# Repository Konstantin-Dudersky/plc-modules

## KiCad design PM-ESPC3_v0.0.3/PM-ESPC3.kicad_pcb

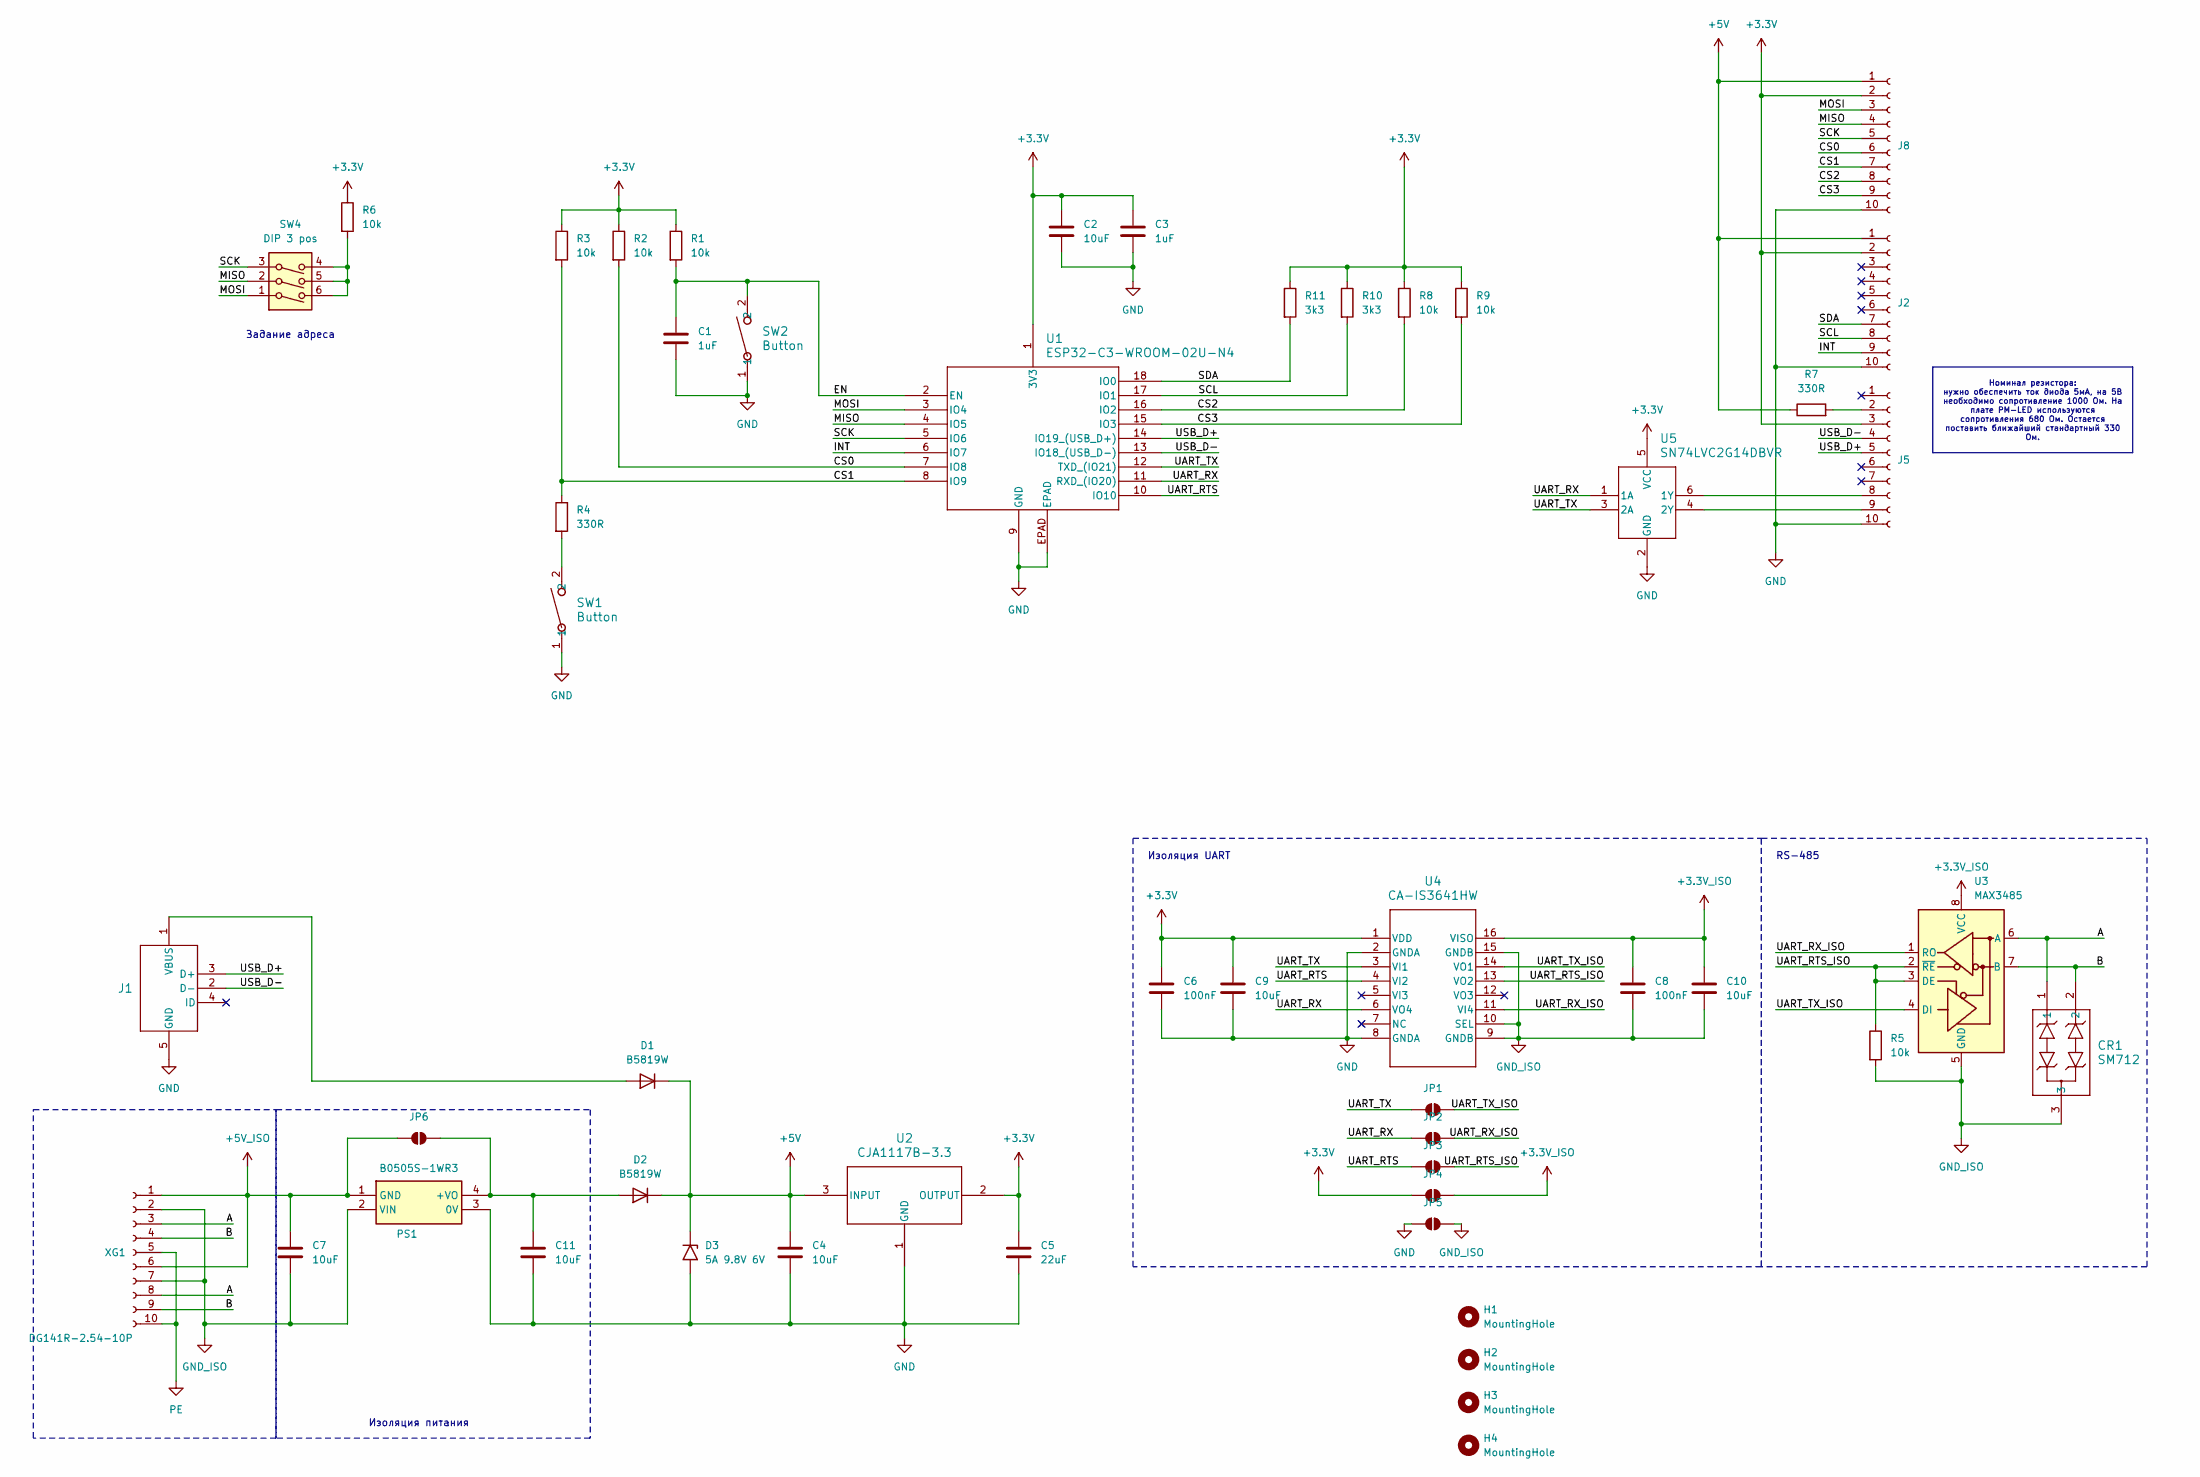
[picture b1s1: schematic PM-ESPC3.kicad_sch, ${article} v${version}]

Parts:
C1, C3: 1uF; C_1206_3216Metric_Pad1.33x1.80mm_HandSolder; part_ipn C_1uF_16V_1206
C2, C4, C7, C9, C10, C11: 10uF; C_1206_3216Metric_Pad1.33x1.80mm_HandSolder; part_ipn C_10uF_16V_1206
C5: 22uF; C_1206_3216Metric_Pad1.33x1.80mm_HandSolder; part_ipn C_22uF_16V_1206
C6, C8: 100nF; C_1206_3216Metric_Pad1.33x1.80mm_HandSolder; part_ipn C_100nF_50V_1206
CR1: SM712; SOT23-3_LTF
D1, D2: B5819W; D_SOD-123; part_ipn B5819W
D3: 5A 9.8V 6V; D_SOD-323_HandSoldering; part_ipn LESD3Z5.0T1G
H1, H2, H3, H4: MountingHole; MountingHole_2.1mm
J1: U254-051T-4BH83-S1S; CONN5_H83-S1S_XKB; part_ipn U254-051T-4BH83-S1S
J2, J5, J8: AFA07-S10FCC-00; CONN10_AFA07-S10_JUS; part_ipn AFA07-S10FCC-00
JP1, JP2, JP3, JP4, JP5, JP6: SolderJumper_2_Open; SolderJumper-2_P1.3mm_Open_RoundedPad1.0x1.5mm
PS1: B0505S-1WR3; B0505S1WR3; Manufacturer_Part_Number B0505S-1WR3
R1, R2, R3, R5, R6, R8, R9: 10k; R_1206_3216Metric_Pad1.30x1.75mm_HandSolder; part_ipn R_10k_1206_1%
R4, R7: 330R; R_1206_3216Metric_Pad1.30x1.75mm_HandSolder; part_ipn R_330R_1206_1%
R10, R11: 3k3; R_1206_3216Metric_Pad1.30x1.75mm_HandSolder; part_ipn R_3k3_1206_1%
SW1, SW2: Button; SW_TS-1088_XNP-M; part_ipn TS-1088-AR02016
SW4: DIP 3 pos; DA03BLP; part_ipn DA-03BLP
U1: ESP32-C3-WROOM-02U-N4; ESP32-C3-WROOM-02U_EXP; part_ipn ESP32-C3-WROOM-02U-N4
U2: CJA1117B-3.3; SOT-89-3; part_ipn CJA1117B-3.3
U3: MAX3485; SOIC-8_3.9x4.9mm_P1.27mm
U4: CA-IS3641HW; SOIC16-WBW_CLG-M; part_ipn CA-IS3641HW
U5: SN74LVC2G14DBVR; DBV6-M
XG1: DG141R-2.54-10P; part_ipn DG141R-2.54-10P

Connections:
+3.3V: C2.2, C3.1, C5.1, C6.1, C9.1, J2.2, J5.3, J8.2, JP4.1 (A), R1.1, R2.1, R3.1, R6.1, R8.1, R9.1, R10.1, R11.1, U1.1 (3V3), U2.2 (OUTPUT), U4.1 (VDD), U5.5 (VCC)
+3.3V_ISO: C8.1, C10.1, JP4.2 (B), U3.8 (VCC), U4.16 (VISO)
+5V: C4.1, D1.1 (K), D2.1 (K), D3.1 (A1), J2.1, J8.1, R7.1, U2.3 (INPUT)
+5V_ISO: C7.1, JP6.1 (A), PS1.1 (GND), XG1.1, XG1.6
/A: CR1.1, U3.6 (A), XG1.3, XG1.8
/B: CR1.2, U3.7 (B), XG1.4, XG1.9
/CS0: J8.6, R2.2, U1.7 (IO8)
/CS1: J8.7, R3.2, R4.1, U1.8 (IO9)
/CS2: J8.8, R8.2, U1.16 (IO2)
/CS3: J8.9, R9.2, U1.15 (IO3)
/EN: C1.1, R1.2, SW2.2, U1.2 (EN)
/INT: J2.9, U1.6 (IO7)
/MISO: J8.4, SW4.2, U1.4 (IO5)
/MOSI: J8.3, SW4.1, U1.3 (IO4)
/SCK: J8.5, SW4.3, U1.5 (IO6)
/SCL: J2.8, R10.2, U1.17 (IO1)
/SDA: J2.7, R11.2, U1.18 (IO0)
/UART_RTS: JP3.1 (A), U1.10 (IO10), U4.4 (VI2)
/UART_RTS_ISO: JP3.2 (B), R5.1, U3.2 (~RE), U3.3 (DE), U4.13 (VO2)
/UART_RX: JP2.1 (A), U1.11 (RXD_(IO20)), U4.6 (VO4), U5.1 (1A)
/UART_RX_ISO: JP2.2 (B), U3.1 (RO), U4.11 (VI4)
/UART_TX: JP1.1 (A), U1.12 (TXD_(IO21)), U4.3 (VI1), U5.3 (2A)
/UART_TX_ISO: JP1.2 (B), U3.4 (DI), U4.14 (VO1)
/USB_D+: J1.3 (D+), J5.5, U1.14 (IO19_(USB_D+))
/USB_D-: J1.2 (D-), J5.4, U1.13 (IO18_(USB_D-))
GND: C1.2, C2.1, C3.2, C4.2, C5.2, C6.2, C9.2, C11.2, D3.2 (A2), J1.5 (GND), J2.10, J5.10, J8.10, JP5.1 (A), PS1.3 (0V), SW1.1, SW2.1, U1.9 (GND), U1.EPAD, U2.1 (GND), U4.2 (GNDA), U4.8 (GNDA), U5.2 (GND)
GND_ISO: C7.2, C8.2, C10.2, CR1.3, JP5.2 (B), PS1.2 (VIN), R5.2, U3.5 (GND), U4.9 (GNDB), U4.10 (SEL), U4.15 (GNDB), XG1.2, XG1.7
unnamed: D1.2 (A), J1.1 (VBUS)
unnamed: C11.1, D2.2 (A), JP6.2 (B), PS1.4 (+VO)
unnamed: J5.2, R7.2
unnamed: J5.8, U5.6 (1Y)
unnamed: J5.9, U5.4 (2Y)
unnamed: R4.2, SW1.2
unnamed: R6.2, SW4.4, SW4.5, SW4.6
PE: XG1.5, XG1.10

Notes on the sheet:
Номинал резистора: нужно обеспечить ток диода 5мА, на 5В необходимо сопротивление 1000 Ом. На плате PM-LED используются сопротивления 680 Ом. Остается поставить ближайший стандартный 330 Ом.
Задание адреса
RS-485
Изоляция UART
Изоляция питания

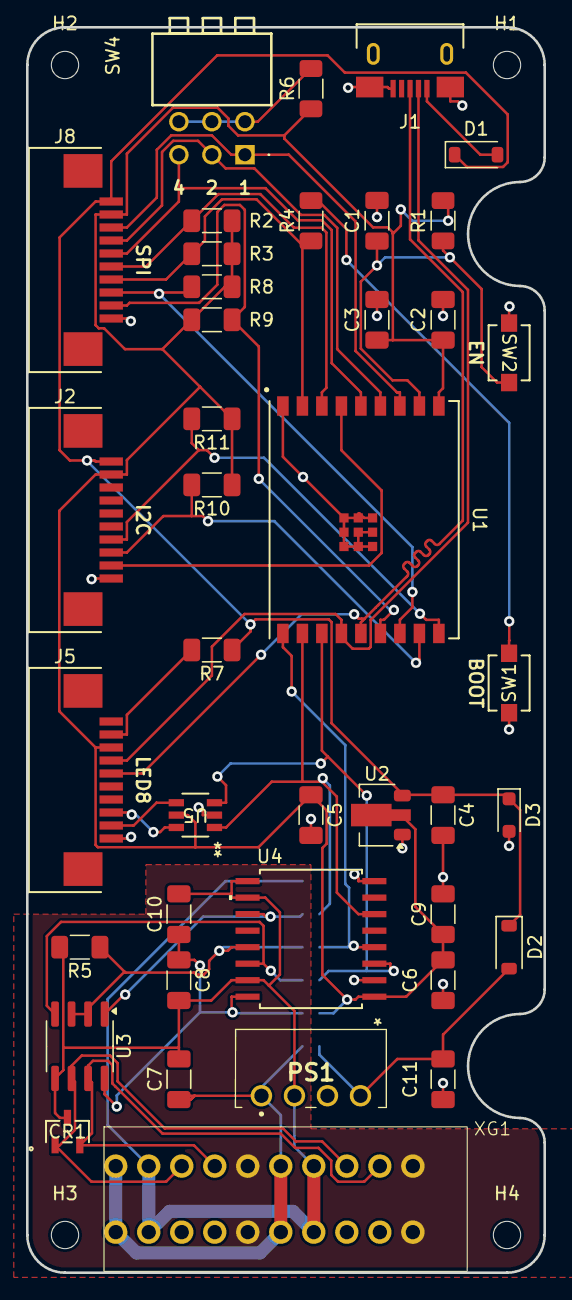
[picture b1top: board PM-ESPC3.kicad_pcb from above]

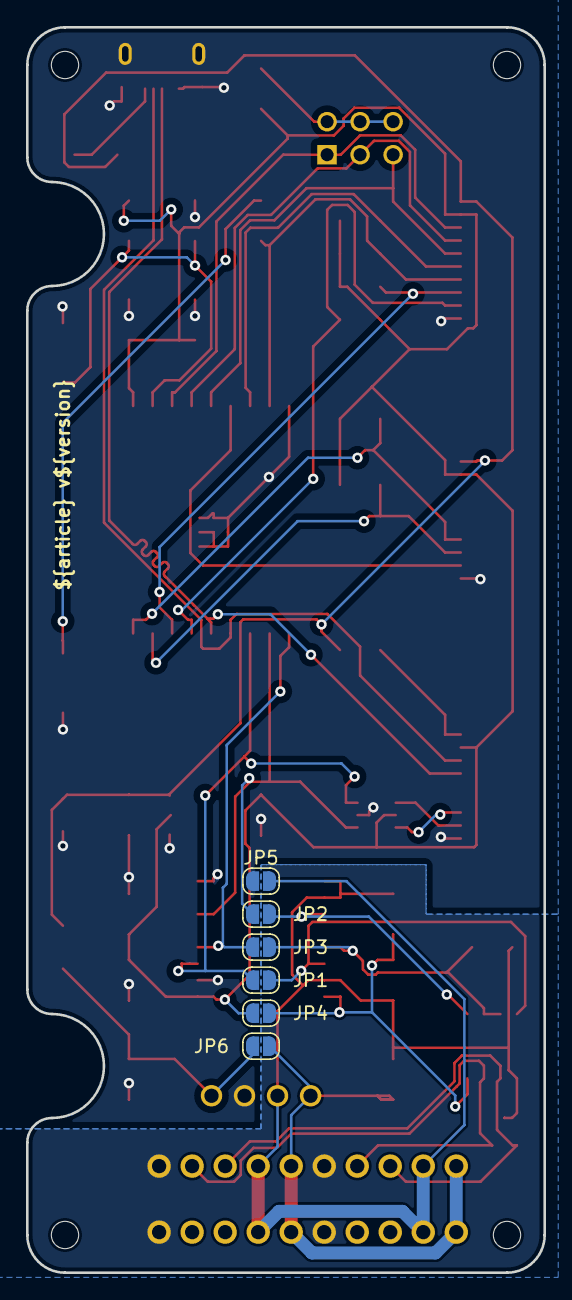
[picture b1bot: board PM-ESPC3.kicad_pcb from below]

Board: 2 copper layers, 39.8 x 95.8 mm, 50 parts (6 on the bottom side), 35 nets.

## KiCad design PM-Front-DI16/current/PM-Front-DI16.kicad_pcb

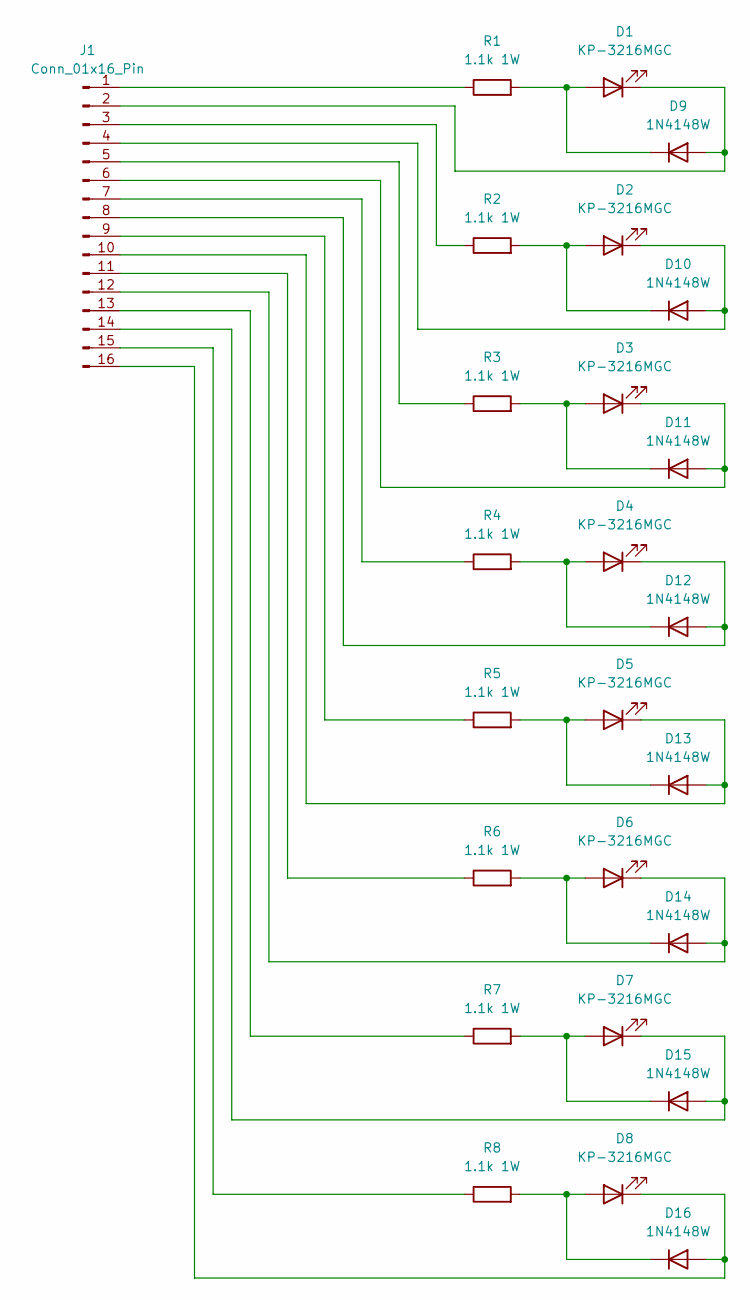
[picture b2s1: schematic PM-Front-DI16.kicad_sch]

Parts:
D1, D2, D3, D4, D5, D6, D7, D8: KP-3216MGC; LED_1206_3216Metric; MfrPart KP-3216MGC
D9, D10, D11, D12, D13, D14, D15, D16: 1N4148W; D_SOD-123; MfrPart 1N4148W
J1: Conn_01x16_Pin; PinHeader_1x16_P2.54mm_Horizontal
R1, R2, R3, R4, R5, R6, R7, R8: 1.1k 1W; R_2512_6332Metric_Pad1.40x3.35mm_HandSolder; MfgPart FRC2512F1101TS

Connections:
unnamed: D1.2 (A), D9.1 (K), R1.2
unnamed: D1.1 (K), D9.2 (A), J1.2
unnamed: D2.1 (K), D10.2 (A), J1.4
unnamed: D2.2 (A), D10.1 (K), R2.2
unnamed: D3.1 (K), D11.2 (A), J1.6
unnamed: D3.2 (A), D11.1 (K), R3.2
unnamed: D4.1 (K), D12.2 (A), J1.8
unnamed: D4.2 (A), D12.1 (K), R4.2
unnamed: D5.1 (K), D13.2 (A), J1.10
unnamed: D5.2 (A), D13.1 (K), R5.2
unnamed: D6.1 (K), D14.2 (A), J1.12
unnamed: D6.2 (A), D14.1 (K), R6.2
unnamed: D7.1 (K), D15.2 (A), J1.14
unnamed: D7.2 (A), D15.1 (K), R7.2
unnamed: D8.1 (K), D16.2 (A), J1.16
unnamed: D8.2 (A), D16.1 (K), R8.2
unnamed: J1.1, R1.1
unnamed: J1.3, R2.1
unnamed: J1.5, R3.1
unnamed: J1.7, R4.1
unnamed: J1.9, R5.1
unnamed: J1.11, R6.1
unnamed: J1.13, R7.1
unnamed: J1.15, R8.1

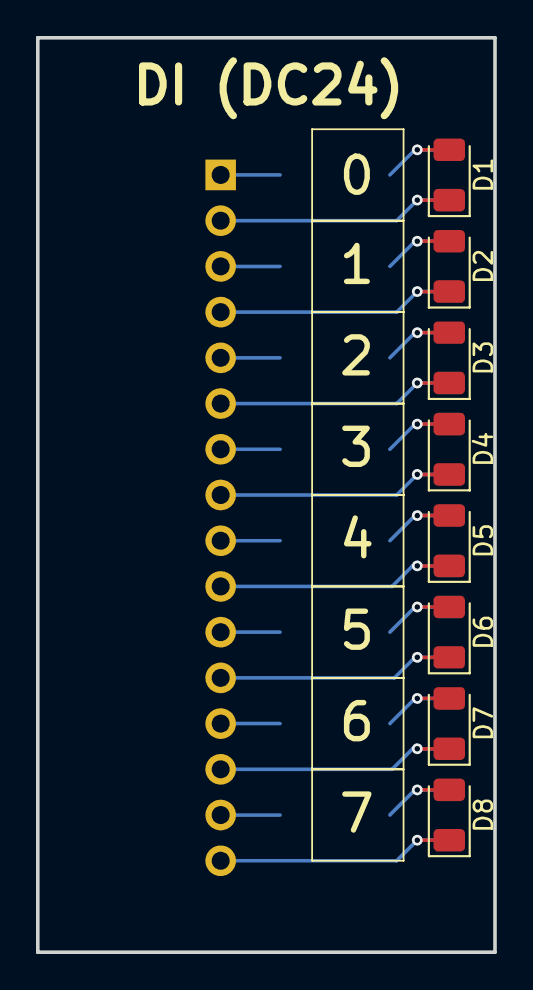
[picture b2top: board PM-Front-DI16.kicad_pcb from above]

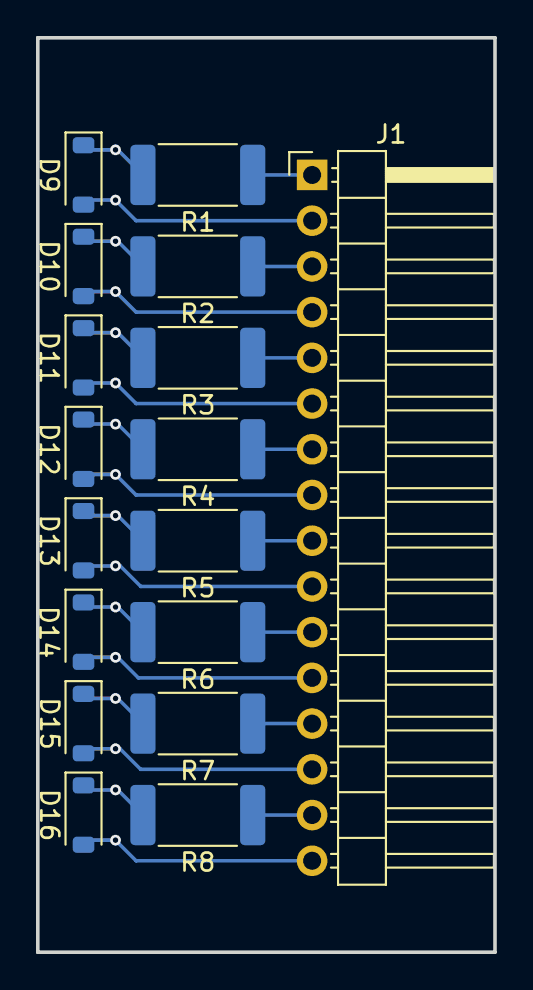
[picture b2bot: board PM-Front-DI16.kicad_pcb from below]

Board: 2 copper layers, 25.4 x 50.8 mm, 25 parts (17 on the bottom side), 24 nets.

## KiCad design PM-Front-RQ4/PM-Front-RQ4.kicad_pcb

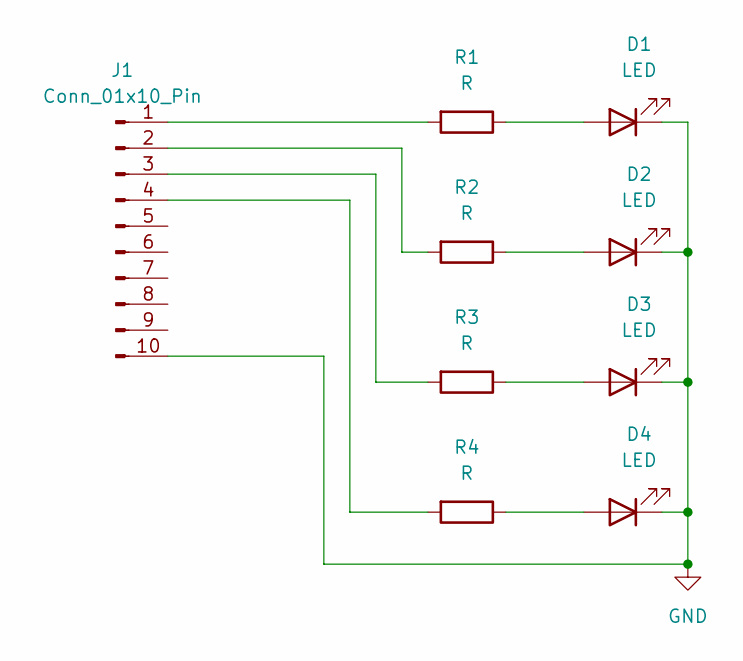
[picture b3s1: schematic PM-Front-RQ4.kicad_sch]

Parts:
D1, D2, D3, D4: LED; LED_1206_3216Metric
J1: Conn_01x10_Pin; PinHeader_1x10_P2.54mm_Horizontal
R1, R2, R3, R4: R; R_1206_3216Metric_Pad1.30x1.75mm_HandSolder

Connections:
GND: D1.1 (K), D2.1 (K), D3.1 (K), D4.1 (K), J1.10
unnamed: D1.2 (A), R1.1
unnamed: D2.2 (A), R2.1
unnamed: D3.2 (A), R3.1
unnamed: D4.2 (A), R4.1
unnamed: J1.1, R1.2
unnamed: J1.2, R2.2
unnamed: J1.3, R3.2
unnamed: J1.4, R4.2

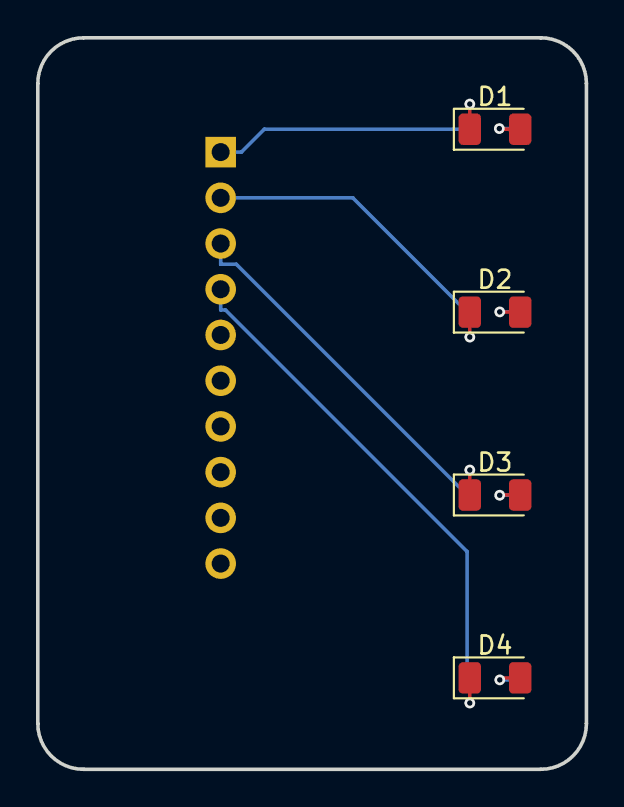
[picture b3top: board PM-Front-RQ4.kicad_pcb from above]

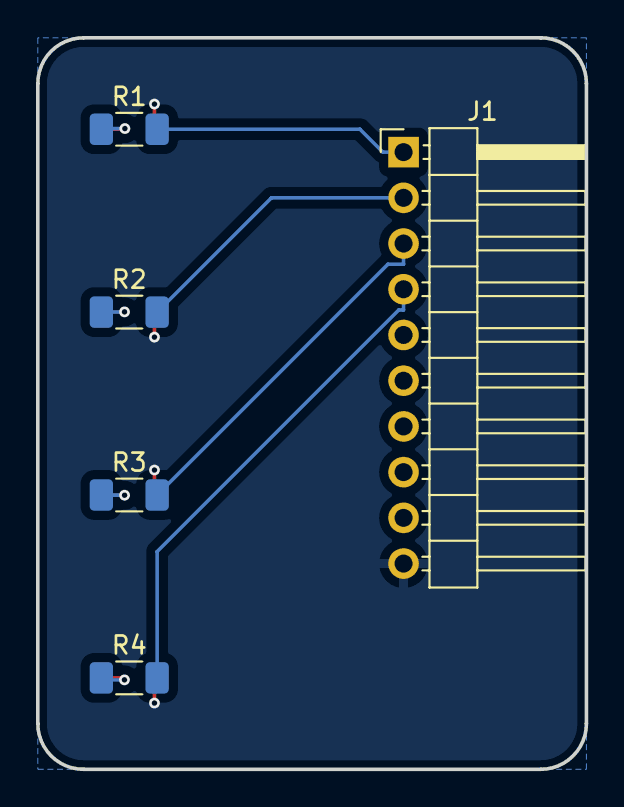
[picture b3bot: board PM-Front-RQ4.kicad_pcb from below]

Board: 2 copper layers, 30.5 x 40.6 mm, 9 parts (5 on the bottom side), 9 nets.

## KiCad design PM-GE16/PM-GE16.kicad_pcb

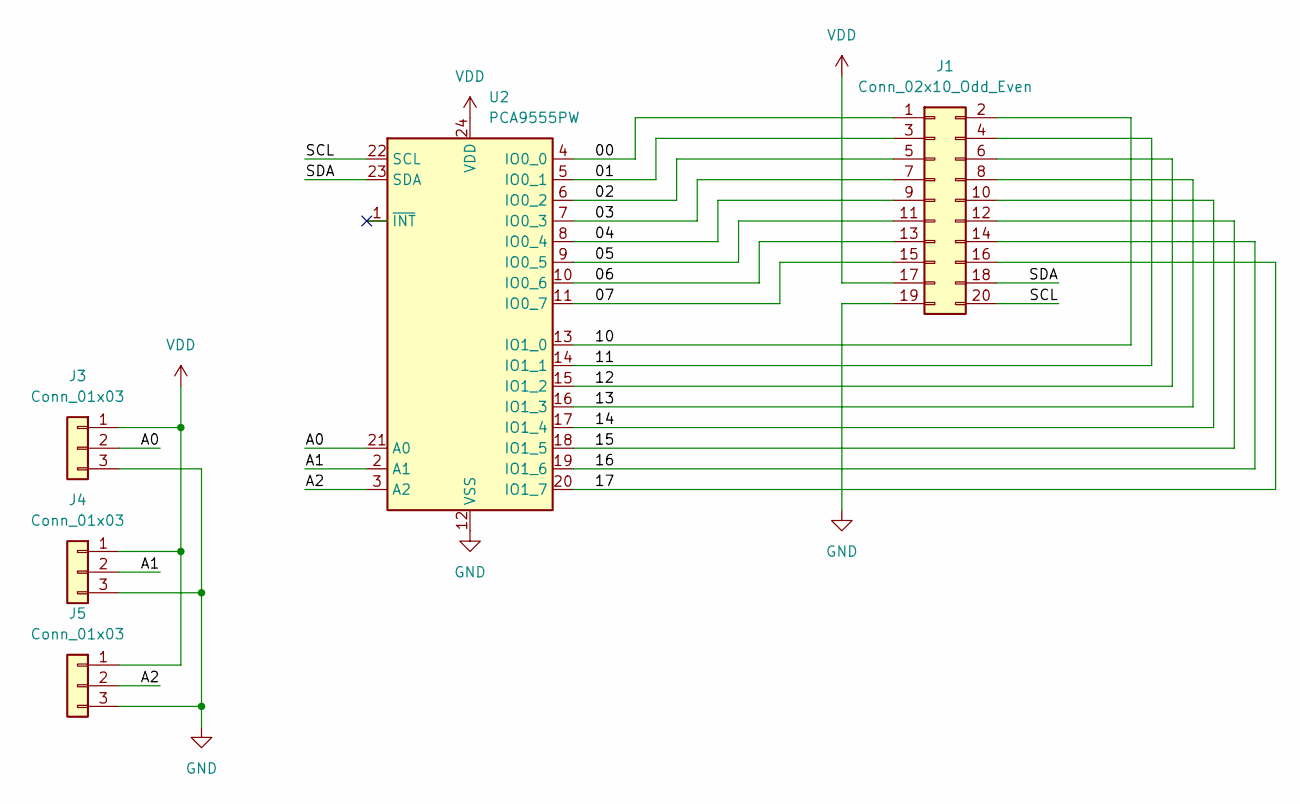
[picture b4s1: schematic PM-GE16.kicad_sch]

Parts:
J1: Conn_02x10_Odd_Even; PinHeader_2x10_P2.54mm_Vertical_SMD
J3, J4, J5: Conn_01x03; PinHeader_1x03_P2.54mm_Vertical_SMD_Pin1Left
U2: PCA9555PW; TSSOP-24_4.4x7.8mm_P0.65mm; MPN PCA9555PW

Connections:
/00: J1.1, U2.4 (IO0_0)
/01: J1.3, U2.5 (IO0_1)
/02: J1.5, U2.6 (IO0_2)
/03: J1.7, U2.7 (IO0_3)
/04: J1.9, U2.8 (IO0_4)
/05: J1.11, U2.9 (IO0_5)
/06: J1.13, U2.10 (IO0_6)
/07: J1.15, U2.11 (IO0_7)
/10: J1.2, U2.13 (IO1_0)
/11: J1.4, U2.14 (IO1_1)
/12: J1.6, U2.15 (IO1_2)
/13: J1.8, U2.16 (IO1_3)
/14: J1.10, U2.17 (IO1_4)
/15: J1.12, U2.18 (IO1_5)
/16: J1.14, U2.19 (IO1_6)
/17: J1.16, U2.20 (IO1_7)
/A0: J3.2, U2.21 (A0)
/A1: J4.2, U2.2 (A1)
/A2: J5.2, U2.3 (A2)
/SCL: J1.20, U2.22 (SCL)
/SDA: J1.18, U2.23 (SDA)
GND: J1.19, J3.3, J4.3, J5.3, U2.12 (VSS)
VDD: J1.17, J3.1, J4.1, J5.1, U2.24 (VDD)

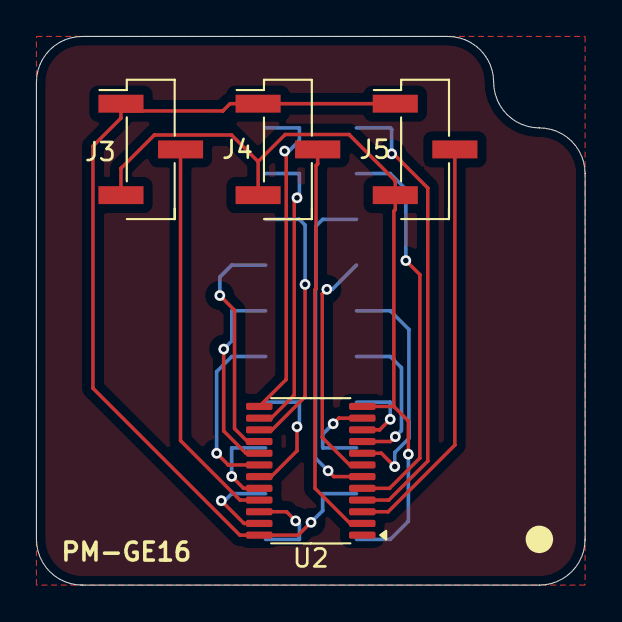
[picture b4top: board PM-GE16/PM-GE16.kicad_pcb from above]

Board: 2 copper layers, 30.5 x 30.5 mm, 5 parts (1 on the bottom side), 23 nets.

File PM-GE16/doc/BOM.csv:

Reference,Value,Footprint,Qty,NextPCB_url,NextPCB_price
J1,Conn_02x10_Odd_Even,Connector_PinHeader_2.54mm:PinHeader_2x10_P2.54mm_Vertical_SMD,1,,
"J3,J4,J5",Conn_01x03,Connector_PinHeader_2.54mm:PinHeader_1x03_P2.54mm_Vertical_SMD_Pin1Left,3,,
U2,PCA9555PW,Package_SO:TSSOP-24_4.4x7.8mm_P0.65mm,1,https://www.hqonline.com/product-detail/enzhipu-nxp--pca9555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,0.75761

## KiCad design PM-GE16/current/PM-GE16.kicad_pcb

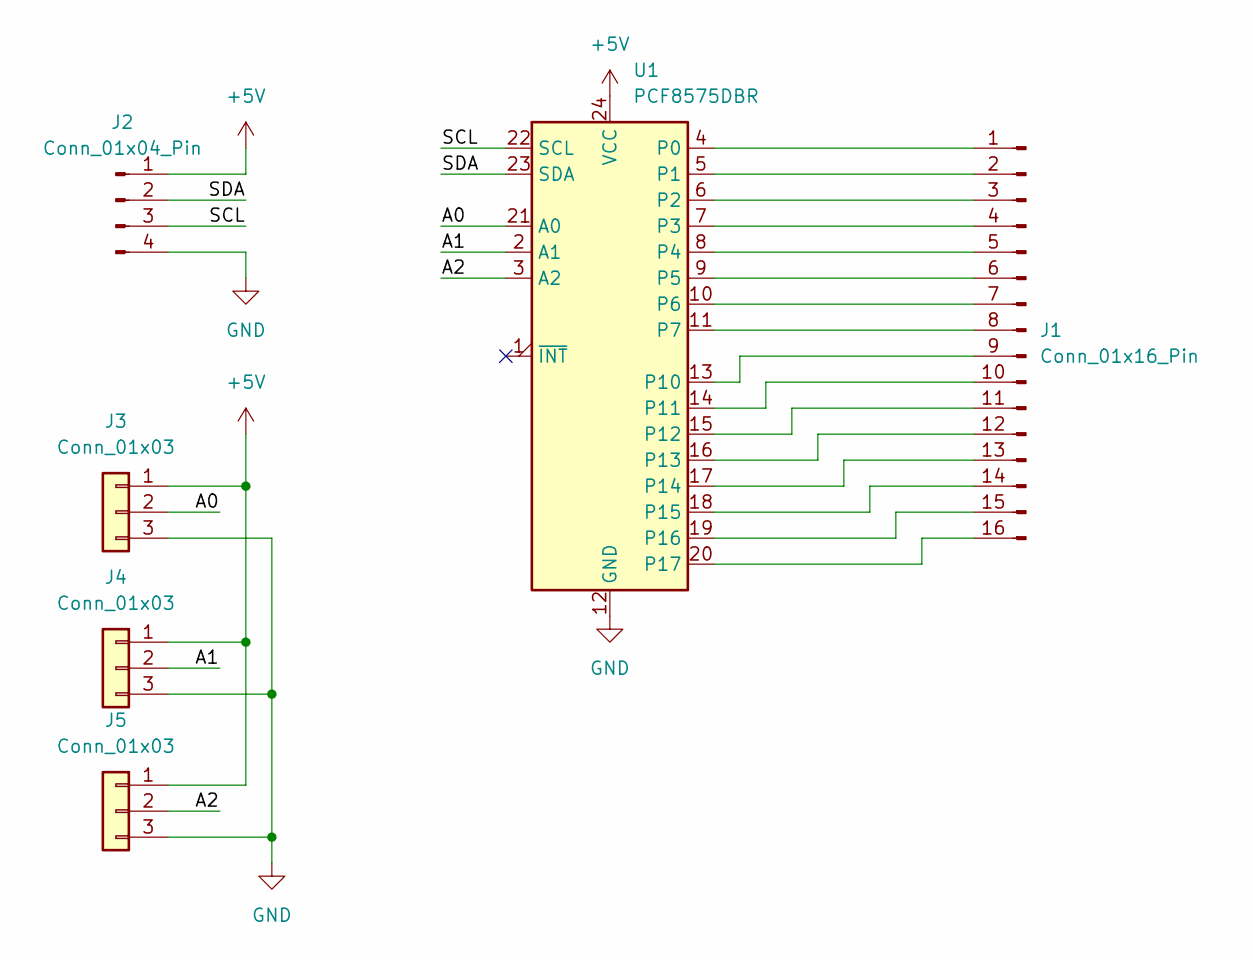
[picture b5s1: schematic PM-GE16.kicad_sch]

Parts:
J1: Conn_01x16_Pin; PinHeader_1x16_P2.54mm_Vertical_SMD_Pin1Left
J2: Conn_01x04_Pin; PinHeader_1x04_P2.54mm_Vertical_SMD_Pin1Left
J3, J4, J5: Conn_01x03; PinHeader_1x03_P2.54mm_Vertical_SMD_Pin1Left
U1: PCF8575DBR; SSOP-24_5.3x8.2mm_P0.65mm

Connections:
+5V: J2.1, J3.1, J4.1, J5.1, U1.24 (VCC)
/A0: J3.2, U1.21 (A0)
/A1: J4.2, U1.2 (A1)
/A2: J5.2, U1.3 (A2)
/SCL: J2.3, U1.22 (SCL)
/SDA: J2.2, U1.23 (SDA)
GND: J2.4, J3.3, J4.3, J5.3, U1.12 (GND)
unnamed: J1.1, U1.4 (P0)
unnamed: J1.2, U1.5 (P1)
unnamed: J1.3, U1.6 (P2)
unnamed: J1.4, U1.7 (P3)
unnamed: J1.5, U1.8 (P4)
unnamed: J1.6, U1.9 (P5)
unnamed: J1.7, U1.10 (P6)
unnamed: J1.8, U1.11 (P7)
unnamed: J1.9, U1.13 (P10)
unnamed: J1.10, U1.14 (P11)
unnamed: J1.11, U1.15 (P12)
unnamed: J1.12, U1.16 (P13)
unnamed: J1.13, U1.17 (P14)
unnamed: J1.14, U1.18 (P15)
unnamed: J1.15, U1.19 (P16)
unnamed: J1.16, U1.20 (P17)

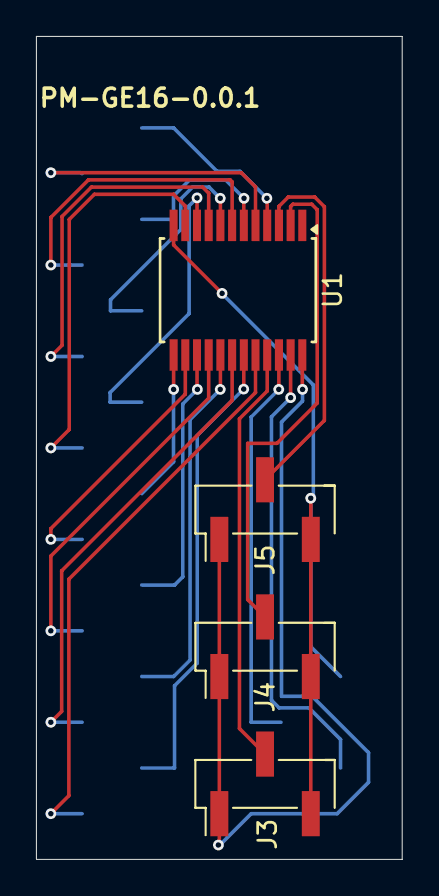
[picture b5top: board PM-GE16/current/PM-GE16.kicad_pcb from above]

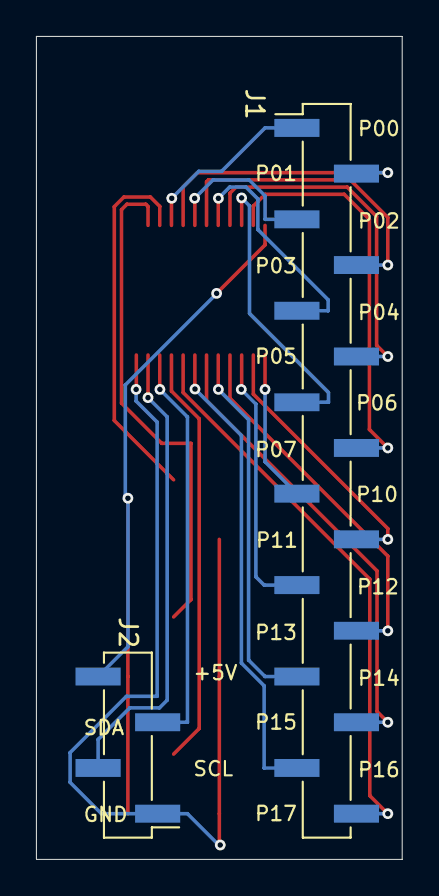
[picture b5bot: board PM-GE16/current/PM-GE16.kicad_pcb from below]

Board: 2 copper layers, 20.3 x 45.7 mm, 6 parts (2 on the bottom side), 23 nets.

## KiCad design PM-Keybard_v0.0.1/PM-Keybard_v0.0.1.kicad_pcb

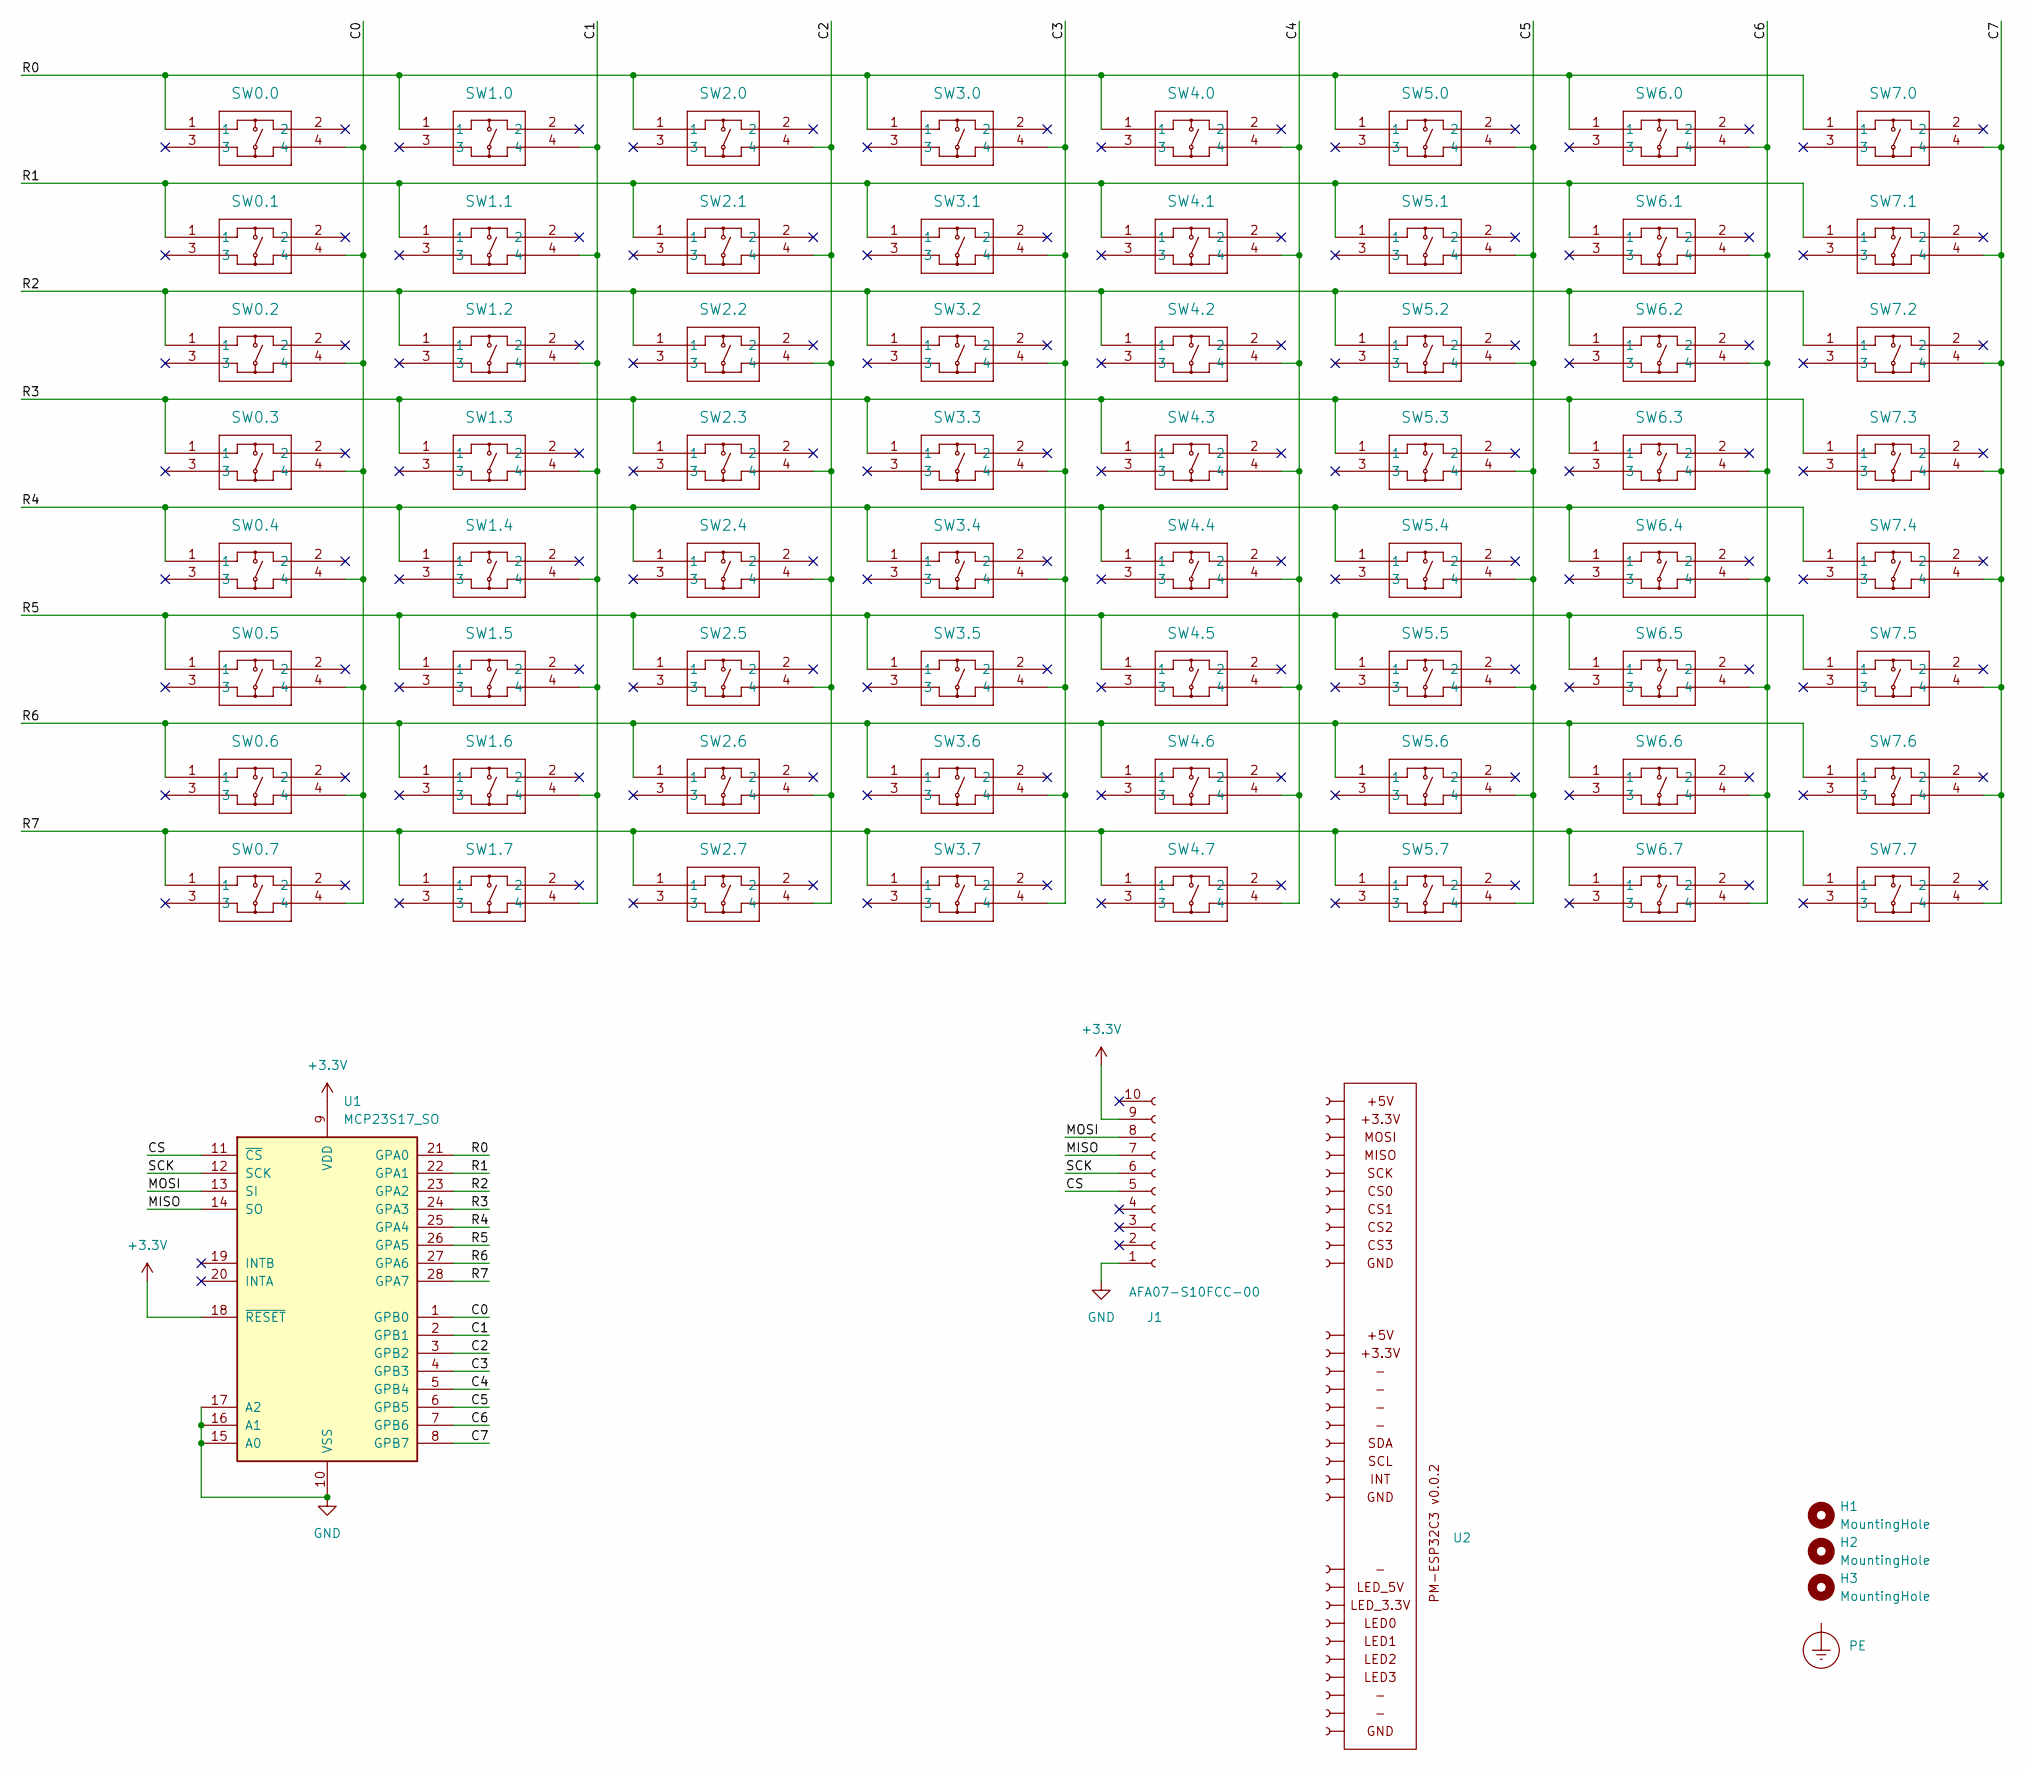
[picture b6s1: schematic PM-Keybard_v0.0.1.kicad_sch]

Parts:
H1, H2, H3: MountingHole; MountingHole_3.2mm_M3
J1: AFA07-S10FCC-00; CONN10_AFA07-S10_JUS
PE1: PE
SW0.0, SW0.1, SW0.2, SW0.3, SW0.4, SW0.5, SW0.6, SW0.7, SW1.0, SW1.1, SW1.2, SW1.3, SW1.4, SW1.5, SW1.6, SW1.7, SW2.0, SW2.1, SW2.2, SW2.3, SW2.4, SW2.5, SW2.6, SW2.7, SW3.0, SW3.1, SW3.2, SW3.3, SW3.4, SW3.5, SW3.6, SW3.7, SW4.0, SW4.1, SW4.2, SW4.3, SW4.4, SW4.5, SW4.6, SW4.7, SW5.0, SW5.1, SW5.2, SW5.3, SW5.4, SW5.5, SW5.6, SW5.7, SW6.0, SW6.1, SW6.2, SW6.3, SW6.4, SW6.5, SW6.6, SW6.7, SW7.0, SW7.1, SW7.2, SW7.3, SW7.4, SW7.5, SW7.6, SW7.7: TS-1187A-B-A-B; TS-1187A-B-A-B_XKB
U1: MCP23S17_SO; SOIC-28W_7.5x17.9mm_P1.27mm; part_ipn MCP23S17-E/SO
U2: PM-ESP32C3_v0.0.2

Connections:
+3.3V: J1.9, U1.9 (VDD), U1.18 (~RESET)
/C0: SW0.0.4, SW0.1.4, SW0.2.4, SW0.3.4, SW0.4.4, SW0.5.4, SW0.6.4, SW0.7.4, U1.1 (GPB0)
/C1: SW1.0.4, SW1.1.4, SW1.2.4, SW1.3.4, SW1.4.4, SW1.5.4, SW1.6.4, SW1.7.4, U1.2 (GPB1)
/C2: SW2.0.4, SW2.1.4, SW2.2.4, SW2.3.4, SW2.4.4, SW2.5.4, SW2.6.4, SW2.7.4, U1.3 (GPB2)
/C3: SW3.0.4, SW3.1.4, SW3.2.4, SW3.3.4, SW3.4.4, SW3.5.4, SW3.6.4, SW3.7.4, U1.4 (GPB3)
/C4: SW4.0.4, SW4.1.4, SW4.2.4, SW4.3.4, SW4.4.4, SW4.5.4, SW4.6.4, SW4.7.4, U1.5 (GPB4)
/C5: SW5.0.4, SW5.1.4, SW5.2.4, SW5.3.4, SW5.4.4, SW5.5.4, SW5.6.4, SW5.7.4, U1.6 (GPB5)
/C6: SW6.0.4, SW6.1.4, SW6.2.4, SW6.3.4, SW6.4.4, SW6.5.4, SW6.6.4, SW6.7.4, U1.7 (GPB6)
/C7: SW7.0.4, SW7.1.4, SW7.2.4, SW7.3.4, SW7.4.4, SW7.5.4, SW7.6.4, SW7.7.4, U1.8 (GPB7)
/CS: J1.5, U1.11 (~CS)
/MISO: J1.7, U1.14 (SO)
/MOSI: J1.8, U1.13 (SI)
/R0: SW0.0.1, SW1.0.1, SW2.0.1, SW3.0.1, SW4.0.1, SW5.0.1, SW6.0.1, SW7.0.1, U1.21 (GPA0)
/R1: SW0.1.1, SW1.1.1, SW2.1.1, SW3.1.1, SW4.1.1, SW5.1.1, SW6.1.1, SW7.1.1, U1.22 (GPA1)
/R2: SW0.2.1, SW1.2.1, SW2.2.1, SW3.2.1, SW4.2.1, SW5.2.1, SW6.2.1, SW7.2.1, U1.23 (GPA2)
/R3: SW0.3.1, SW1.3.1, SW2.3.1, SW3.3.1, SW4.3.1, SW5.3.1, SW6.3.1, SW7.3.1, U1.24 (GPA3)
/R4: SW0.4.1, SW1.4.1, SW2.4.1, SW3.4.1, SW4.4.1, SW5.4.1, SW6.4.1, SW7.4.1, U1.25 (GPA4)
/R5: SW0.5.1, SW1.5.1, SW2.5.1, SW3.5.1, SW4.5.1, SW5.5.1, SW6.5.1, SW7.5.1, U1.26 (GPA5)
/R6: SW0.6.1, SW1.6.1, SW2.6.1, SW3.6.1, SW4.6.1, SW5.6.1, SW6.6.1, SW7.6.1, U1.27 (GPA6)
/R7: SW0.7.1, SW1.7.1, SW2.7.1, SW3.7.1, SW4.7.1, SW5.7.1, SW6.7.1, SW7.7.1, U1.28 (GPA7)
/SCK: J1.6, U1.12 (SCK)
GND: J1.1, U1.10 (VSS), U1.15 (A0), U1.16 (A1), U1.17 (A2)
